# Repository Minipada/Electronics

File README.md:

Electronics
===========

Library
-----------
Here will be much circuits I have made by myself which wil help in robotics or in wearable technology

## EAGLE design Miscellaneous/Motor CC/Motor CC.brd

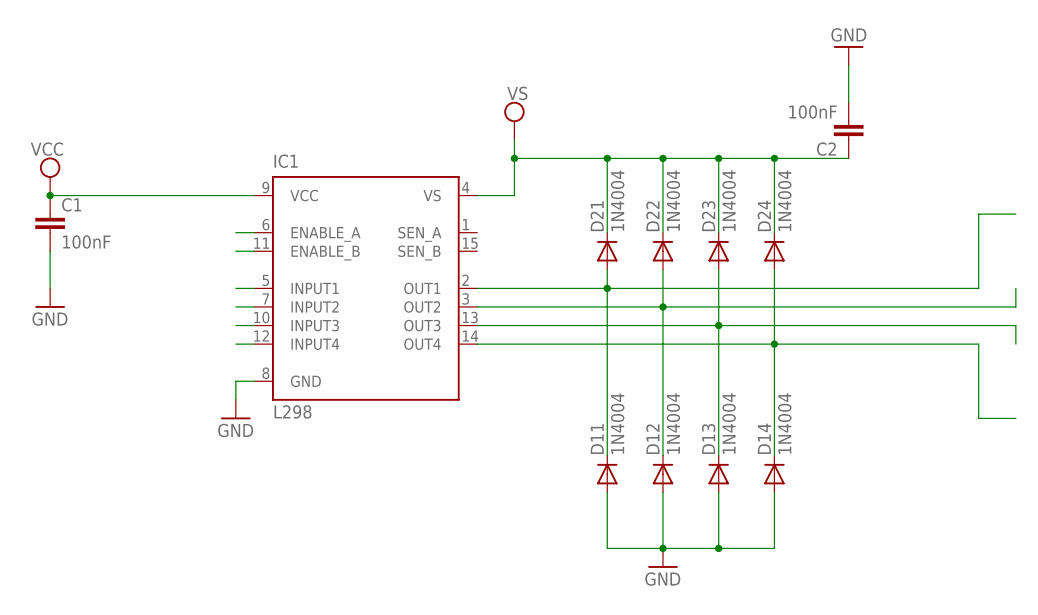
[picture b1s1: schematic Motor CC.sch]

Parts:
C1, C2: 100nF; C025-030X050
D11, D12, D13, D14, D21, D22, D23, D24: 1N4004; DO41-10
IC1: L298; MULTIWATT-15

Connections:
GND: C1.2, C2.2, D11.A, D12.A, D13.A, D14.A, IC1.8 (GND)
unnamed: D14.C, D24.A, IC1.14 (OUT4)
unnamed: D11.C, D21.A, IC1.2 (OUT1)
unnamed: D12.C, D22.A, IC1.3 (OUT2)
unnamed: D13.C, D23.A, IC1.13 (OUT3)
VSS: C1.1, C2.1, D21.C, D22.C, D23.C, D24.C, IC1.4 (VS), IC1.9 (VCC)

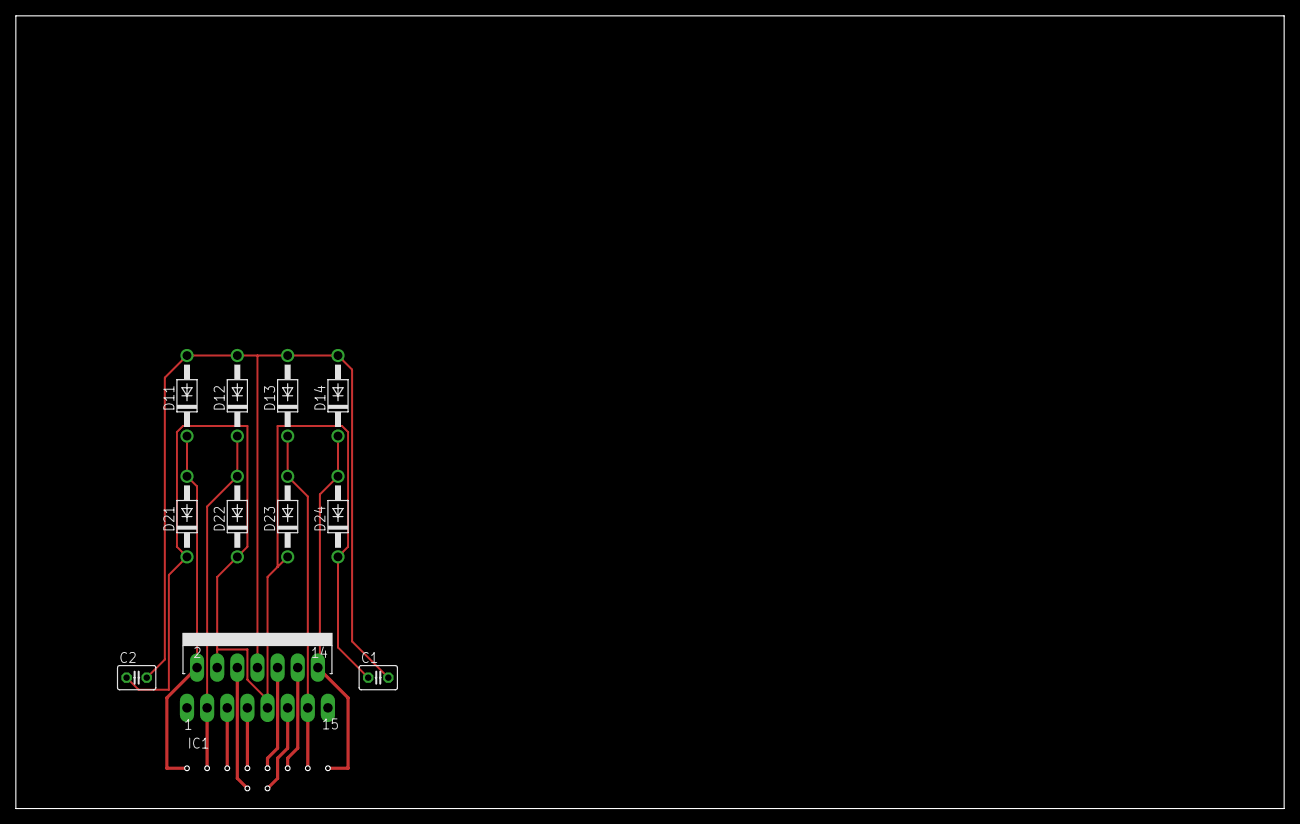
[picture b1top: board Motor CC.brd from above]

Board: 2 copper layers, 160.0 x 100.0 mm, 11 parts (0 on the bottom side), 6 nets.

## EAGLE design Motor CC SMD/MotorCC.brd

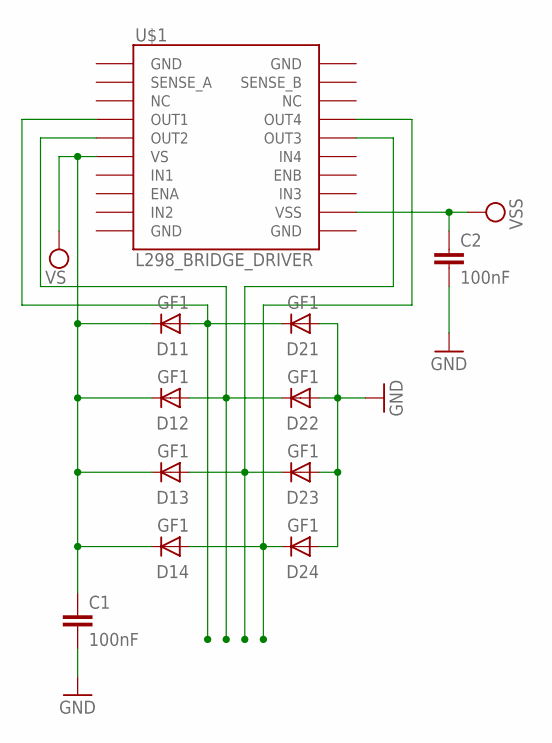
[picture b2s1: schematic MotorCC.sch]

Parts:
C1, C2: 100nF; C0805
D11, D12, D13, D14, D21, D22, D23, D24: GF1; SMA-DO214AC
U$1: L298_BRIDGE_DRIVER; POWERSO20

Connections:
GND: C1.2, C2.2, D21.A, D22.A, D23.A, D24.A
unnamed: D11.A, D21.K (C), U$1.4 (OUT1)
unnamed: D12.A, D22.K (C), U$1.5 (OUT2)
unnamed: D13.A, D23.K (C), U$1.16 (OUT3)
unnamed: D14.A, D24.K (C), U$1.17 (OUT4)
VCC: C2.1, U$1.12 (VSS)
VSS: C1.1, D11.K (C), D12.K (C), D13.K (C), D14.K (C), U$1.6 (VS)

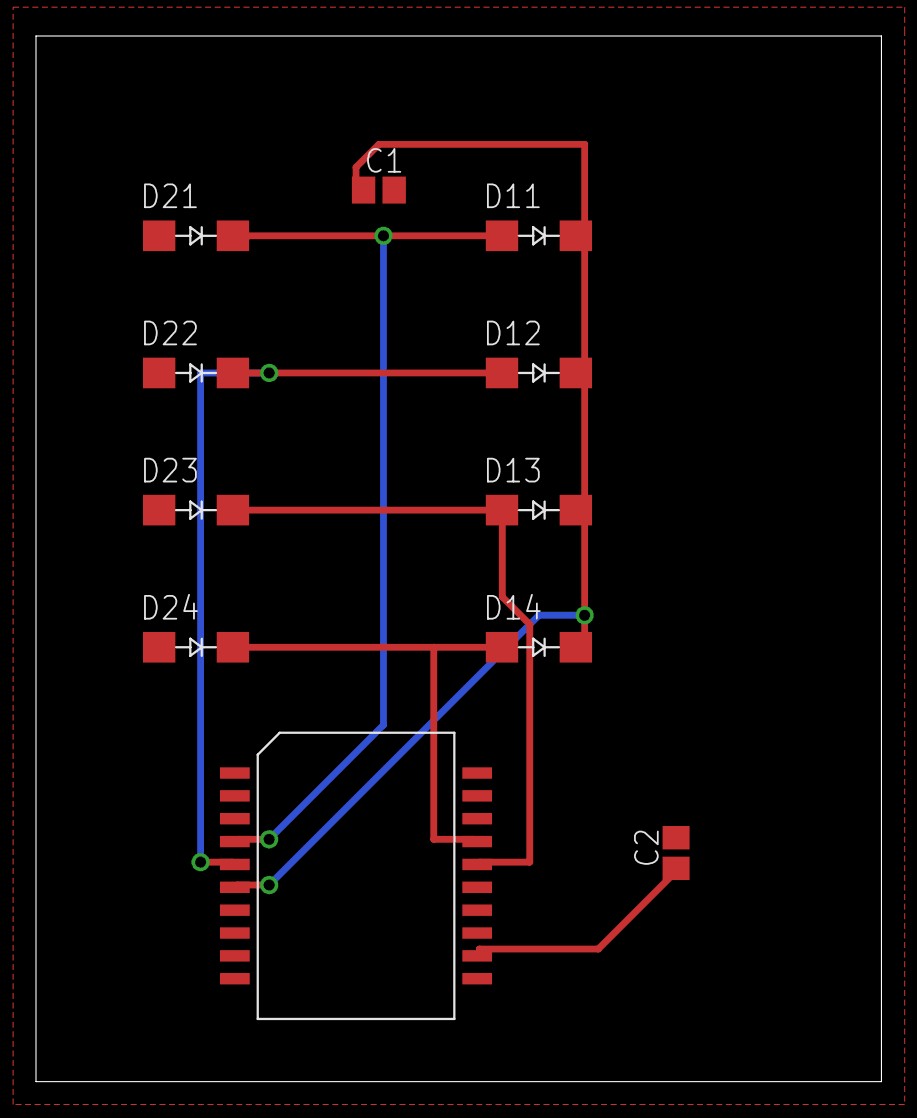
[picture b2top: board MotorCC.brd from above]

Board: 2 copper layers, 47.0 x 58.1 mm, 11 parts (0 on the bottom side), 7 nets.

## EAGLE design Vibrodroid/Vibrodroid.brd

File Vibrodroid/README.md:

Vibrodroid
===========

Not the Vibrodroids from Star wars and neither a sextoy.
These are robots which moves with motor vibrations and following light.

Credits to Association DTRE (asso-dtre.fr and Alexis Soto for the project).
I do the eagle file but they had the idea.

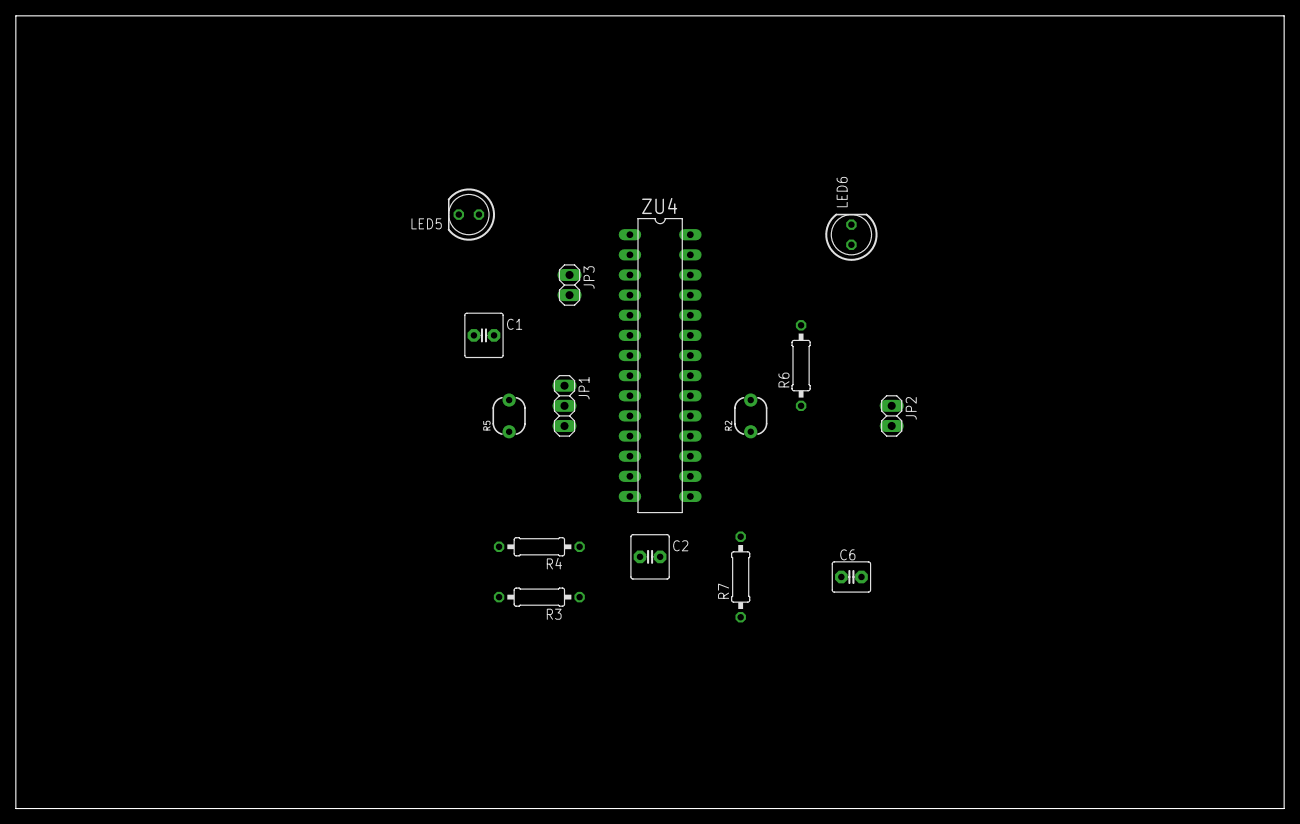
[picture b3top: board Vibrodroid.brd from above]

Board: 2 copper layers, 160.0 x 100.0 mm, 15 parts (0 on the bottom side), 12 nets, no tracks yet.

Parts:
C1, C2: C2.5-6
C6: 100n; C2.5-4
JP1: 1X03
JP2, JP3: 1X02
LED5, LED6: LED5MM
R2, R5: PHOTOCELLPTH; PHOTOCELL
R3, R4: 10k; 0207/10
R6, R7: 0207/10
ZU4: ATMEGA328P-PU; DIL28-3

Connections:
A3: R2.1, R3.2, ZU4.26
A4: R4.2, R5.1, ZU4.27
D13: R6.1, ZU4.19
GND: C1.1, C2.1, C6.1, JP2.1, LED5.K, LED6.K, R2.2, R5.2, ZU4.8, ZU4.22
unnamed: C6.2, ZU4.7, ZU4.20
unnamed: LED5.A, R6.2
unnamed: LED6.A, R7.2
RX: JP3.1, ZU4.2
TX: JP3.2, ZU4.3
VCC: JP2.2, R3.1, R4.1, R7.1
XTAL1: C2.2, JP1.1, ZU4.9
XTAL2: C1.2, JP1.3, ZU4.10

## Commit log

2014-05-04 All my electronics file
    These are all the circuits I 've done with Eagle
2014-05-04 DC Motor control via L298p
2014-05-04 Add the routes now !
2014-05-05 Routes added
2014-05-06 some changes
2014-05-06 Motors DC finished :D
2014-05-08 Starting Vibrodroid !
    Starting a new project
2014-11-27 Added some intel galileo files
2014-11-27 file name corrections
2014-11-30 Some corrections, again
2014-11-30 other organisation
2014-12-06 Edison support
2014-12-06 Edison correction
2014-12-06 again
2014-12-06 added unplug advice
2014-12-06 correction
2014-12-06 just a test
2014-12-06 delet first.txt
2014-12-06 copy linuxmpu9150
2014-12-06 other mpu dl
2014-12-20 Reorganisation - motor Edison
    Added motor code control for Edison, v0.1, need some rework.
    Works in one way on pins 8/9 atm
2015-01-02 Editing names and making motor lib working
2015-01-02 deleting libs - copie, useless
2015-01-03 lib motor works perfectly, and is commented, next !
2015-01-04 adding some tutorials
2015-01-04 2nd test

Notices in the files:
parts and their libraries:
SparkFun-Aesthetics: Licensing: Creative Commons ShareAlike 4.0 International - https://creativecommons.org/licenses/by-sa/4.0
SparkFun: Licensing: CC v3.0 Share-Alike You are welcome to use this library for commercial purposes.
